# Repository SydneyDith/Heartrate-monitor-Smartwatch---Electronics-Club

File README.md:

# Heart rate Monitor Smartwatch - Electronics Club
Led the development of a heart rate monitor smartwatch based on the ATmega328P microcontroller with a group of 4. Utilized several sensors to send/receive data via I2C communication protocol using C based Arduino IDE. Designed custom PCB while analyzing several datasheets to reduce device size and create a more ergonomic user experience. 

This project was separated into two teams. Team 1 specialized in hardware development and was responsible for component selection, power distribution, datasheet analysis and PCB design. Team 2 interfaced with the microcontroller and sensors in the Arduino IDE by utilizing libraries like PulseSensor Playground, U8g2, and RTClib. While I primarily led Team 1, I also served as the mediator for cross-team communication to ensure hardware and software supported each other.

## Smartwatch Project Objectives

| Feature | Description | Goal |
| :--- | :--- | :--- |
| **Heart Rate Monitor** | Integrate Pulse Sensor | Provides heart rate measurements. |
| **OLED Display** | 1.3" SH1106 OLED Display | Clear visual output for biometric data and time. |
| **Timekeeping** | RTC (Real-Time Clock) | Maintain precise time and date. |
| **Power System** | Rechargeable LiPo | Provides rechargeable power. |

Throughout every iteration of this project we may have moved forward with different components that better fit our needs, however, the 4 underlying features above were included in every version of this project. 

## Proof of Concept: ***May 2025***

The image above shows the first prototype of our Smartwatch. This version was based off of Arduino's smallest dev board the Pro Mini which houses the ATmega328P as its microcontroller (we would later use on the final versions of our project). To provide the functionalities we desired, we ordered several Arduino compatible modules that we could power and hook up to specific digital pins on the Pro Mini. In the table below is the comprehensive parts list we used for our first prototype:

| Feature | Part Name | Image |
| :--- | :--- | :--- |
| **Microcontroller** | Arduino Pro Mini |  |
| **Heart Rate Monitor** | Integrate Pulse Sensor | |
| **OLED Display** | OLED Display |  |
| **Timekeeping** | RTC (Real-Time Clock) | |
| **Power System** | Rechargeable LiPo | |

### Pulse Sensors Issues
The OLED display shows time, date, and current heart rate reading. Team 2 was able to program the Pro Mini to read from the RTC module and pulse sensor then display the results on the OLED. The pulse sensor results fluctuated quite a bit. After some research, we attributed this to the quality of the sensor itself. Many cheap pulse sensors use a method called photoplethysmography (PPG) to measure the change in blood volume in your capillaries as your heart beats. The pulse sensor module uses a green LED to shine light into the capillaries and measures the amount of light reflected back using a photodetector. Ideally, the pulse sensor can translate this information into an accurate heart rate reading. PPG is cheap, however, it's very sensitive to real world motion, ambient light interference and sensor contact. 
[*references*](https://www.sciencedirect.com/topics/engineering/sensor-pulse#:~:text=A%20pulse%20sensor%20is%20defined,Arduino%20for%20health%20monitoring%20applications.)

More accurate pulse sensors (professional grade) cost hundreds or thousands of dollars. Luckily, there is a cheaper PPG option, the MAX30102, that uses multi-wavelength LEDs and has an on-board processing IC. It also includes SpO2 readings as an added feature. We later decided to switch to the MAX30102 pulse oximeter to replace the pulse sensor module.

### First Prototype: ***May 2025***
To turn our breadboard prototype into something that resembled a watch, we soldered the modules together trying to keep wires as short as possible. The following video shows the result:

| Top View | Side View 1 | Side View 2 | Video |
| :---: | :---: | :---: | :---: |
|  |  |  | <video src="https://github.com/user-attachments/assets/febb02ad-0546-478b-9966-6aa6d14cd212" width="120" controls></video> |

During this stage of the design process, my team and I realized that size was going to be our main constraint. The form factor shown above is ridiculously large to be comfortably worn on the wrist. After the 3D printed housing, my team and I estimated our first prototype's dimensions would be around 45mm x 45mm x 50mm, which would better be used as a desk clock. After doing more research and conversing amongst ourselves and with our peers, we decided to create a custom PCB that would eliminate many of the unnecessary functions our sensor modules included. For example, the Pro Mini included headers for every I/O pin, only ~5 of which were essential and the DS3231 RTC module included alarm and 32kHz square wave output functionalities that were out of the scope of this project. By creating a custom PCB, we could limit unnecessary functions of our modules, reducing size and creating a more ergonomic design.

## Schematic Design: ***February 2026***

Although we decided to transition to the MAX30102 pulse oximeter, our proof of concept was still valid as we are only replacing the pulse sensor and there are countless resources online showing the MAX30102's compatibility with the 328P. With this, we decided to move forward into PCB design for our second prototype.

To minimize the size of our PCB, we only wanted to include functionalities that were (for the most part) strictly necessary for our smartwatch. We would essentially be stripping the modules from our prototype and putting everything on one PCB. First, we researched the bare minimum requirements for the ATmega328P microcontroller. Using the microcontroller's datasheet and online resources, we were able to simplify the circuit down to a few capacitors and a pull-up resistor. There was an optional 16MHz external crystal oscillator that was typically used with the 328P, however, these clock speeds wouldn't be necessary for our use case. We could instead use the 8 MHz internal oscillator. We used similar techniques to reduce the size of our RTC and sensor modules.

The final schematic for Prototype 2 is shown below: (*see below the image for in-depth detail about the schematic*)

<p align="center">
  <a href="./images/schem.pdf">📄 View Full Schematic (PDF)</a>
</p>

To use the 328P's 8 MHz internal clock, we were required to run the microcontroller at 3.3V, however, our LiPo was 4.2V-3.7V. To fix this, we simply included a 3.3V Low Dropout regulator (LDO) (U2) after the power switch. This reduced our input voltage to a clean 3.3V. Additionally, the MAX30102 operates at 1.8V, so we included a second LDO (U5) that reduced the 3.3V line to 1.8V which could be used for the pulse oximeter's input voltage. However, every other IC was powered by the 3.3V line. The I2C communication lines from the RTC and pulse oximeter required two 4.7k pull-up resistors to the 3.3V line as per the datasheets. We also included several input capacitors and decoupling capacitors on the RTC and pulse oximeter as the datasheet heavily recommended or required them. 

We also included 4 pin headers: I2C clock, I2C data, +3.3V, and GND for the SH1106 OLED display. We plan to solder the 4 required pins directly to the OLED module used in the previous prototype. 

Since there is no longer a Micro USB port on our microcontroller (like the Pro Mini), we must use a [USB to Serial Converter](https://www.amazon.com/NOYITO-CP2102-Converter-Downloader-Arduino/dp/B07D54K82D) so we can connect and upload code to the 328P using UART communication. 

Upon doing further research on the microcontroller, we encountered a problem. Factory new ATmega328P chips often do not come with a pre-installed bootloader. The bootloader is an essential piece of software that allows the microcontroller to communicate via UART. Without UART communication, we would not be able to upload our code using the USB to serial converter. We researched methods to solve this issue. We found a process called In-System Programming (ISP) that requires an Arduino to flash the bootloader onto a blank ATmega328P. To do this we simply created 4 more pin headers that connected to specific pins on the 328P. These were: MOSI, MISO, SCK, and RESET. Using these four SPI pins alongside +3.3V, and GND, we could successfully bootload the chip using an external Arduino Nano allowing us to program through UART communication.
[Bootloader Procedure (PDF)](images/Smartwatch%20Bootloader%20Procedure.pdf).

## PCB Design: ***April 2026***

Final PCB design: (46mm x 39mm x 5mm)

| Front PCB view (*OLED will be connected to the 4 pinheaders*) | Back PCB view |
| :---: | :---: |
|  |  |

The images and 3D renders above show the final PCB design for Prototype 2. Now I plan to move on to the assembly phase when the PCB and components arrive in the coming weeks.
## TO DO

- [ ] **Bootload the ATmega328P**
    - Follow the [bootloader procedure](images/Smartwatch%20Bootloader%20Procedure.pdf)
    - Ensure the microcontroller communicates via UART
    - Test Blink sketch with on-board LED
- [ ] **Initial Soldering & Assembly**
    - Solder MAX30102 and coin cell battery using a heat gun
    - Assemble the remainder of the PCB
    - Verify MAX30102 has a clear line of sight to the user's skin
- [ ] **Sensor Testing**
    - [ ] Pulse Oximeter: Verify accurate heart rate/SpO2 readings
    - [ ] OLED: Ensure proper display rendering
    - [ ] RTC: Confirm accurate timekeeping
- [ ] **Power System Setup**
    - Integrate LiPo battery and external charging circuit
- [ ] **Performance Testing**
    - [ ] Heart rate accuracy
    - [ ] Battery life duration
    - [ ] Charge time verification
- [ ] **Housing**
    - Design 3D printed enclosure
- [ ] **Interpret Tests**
    - Document changes for Prototype 3

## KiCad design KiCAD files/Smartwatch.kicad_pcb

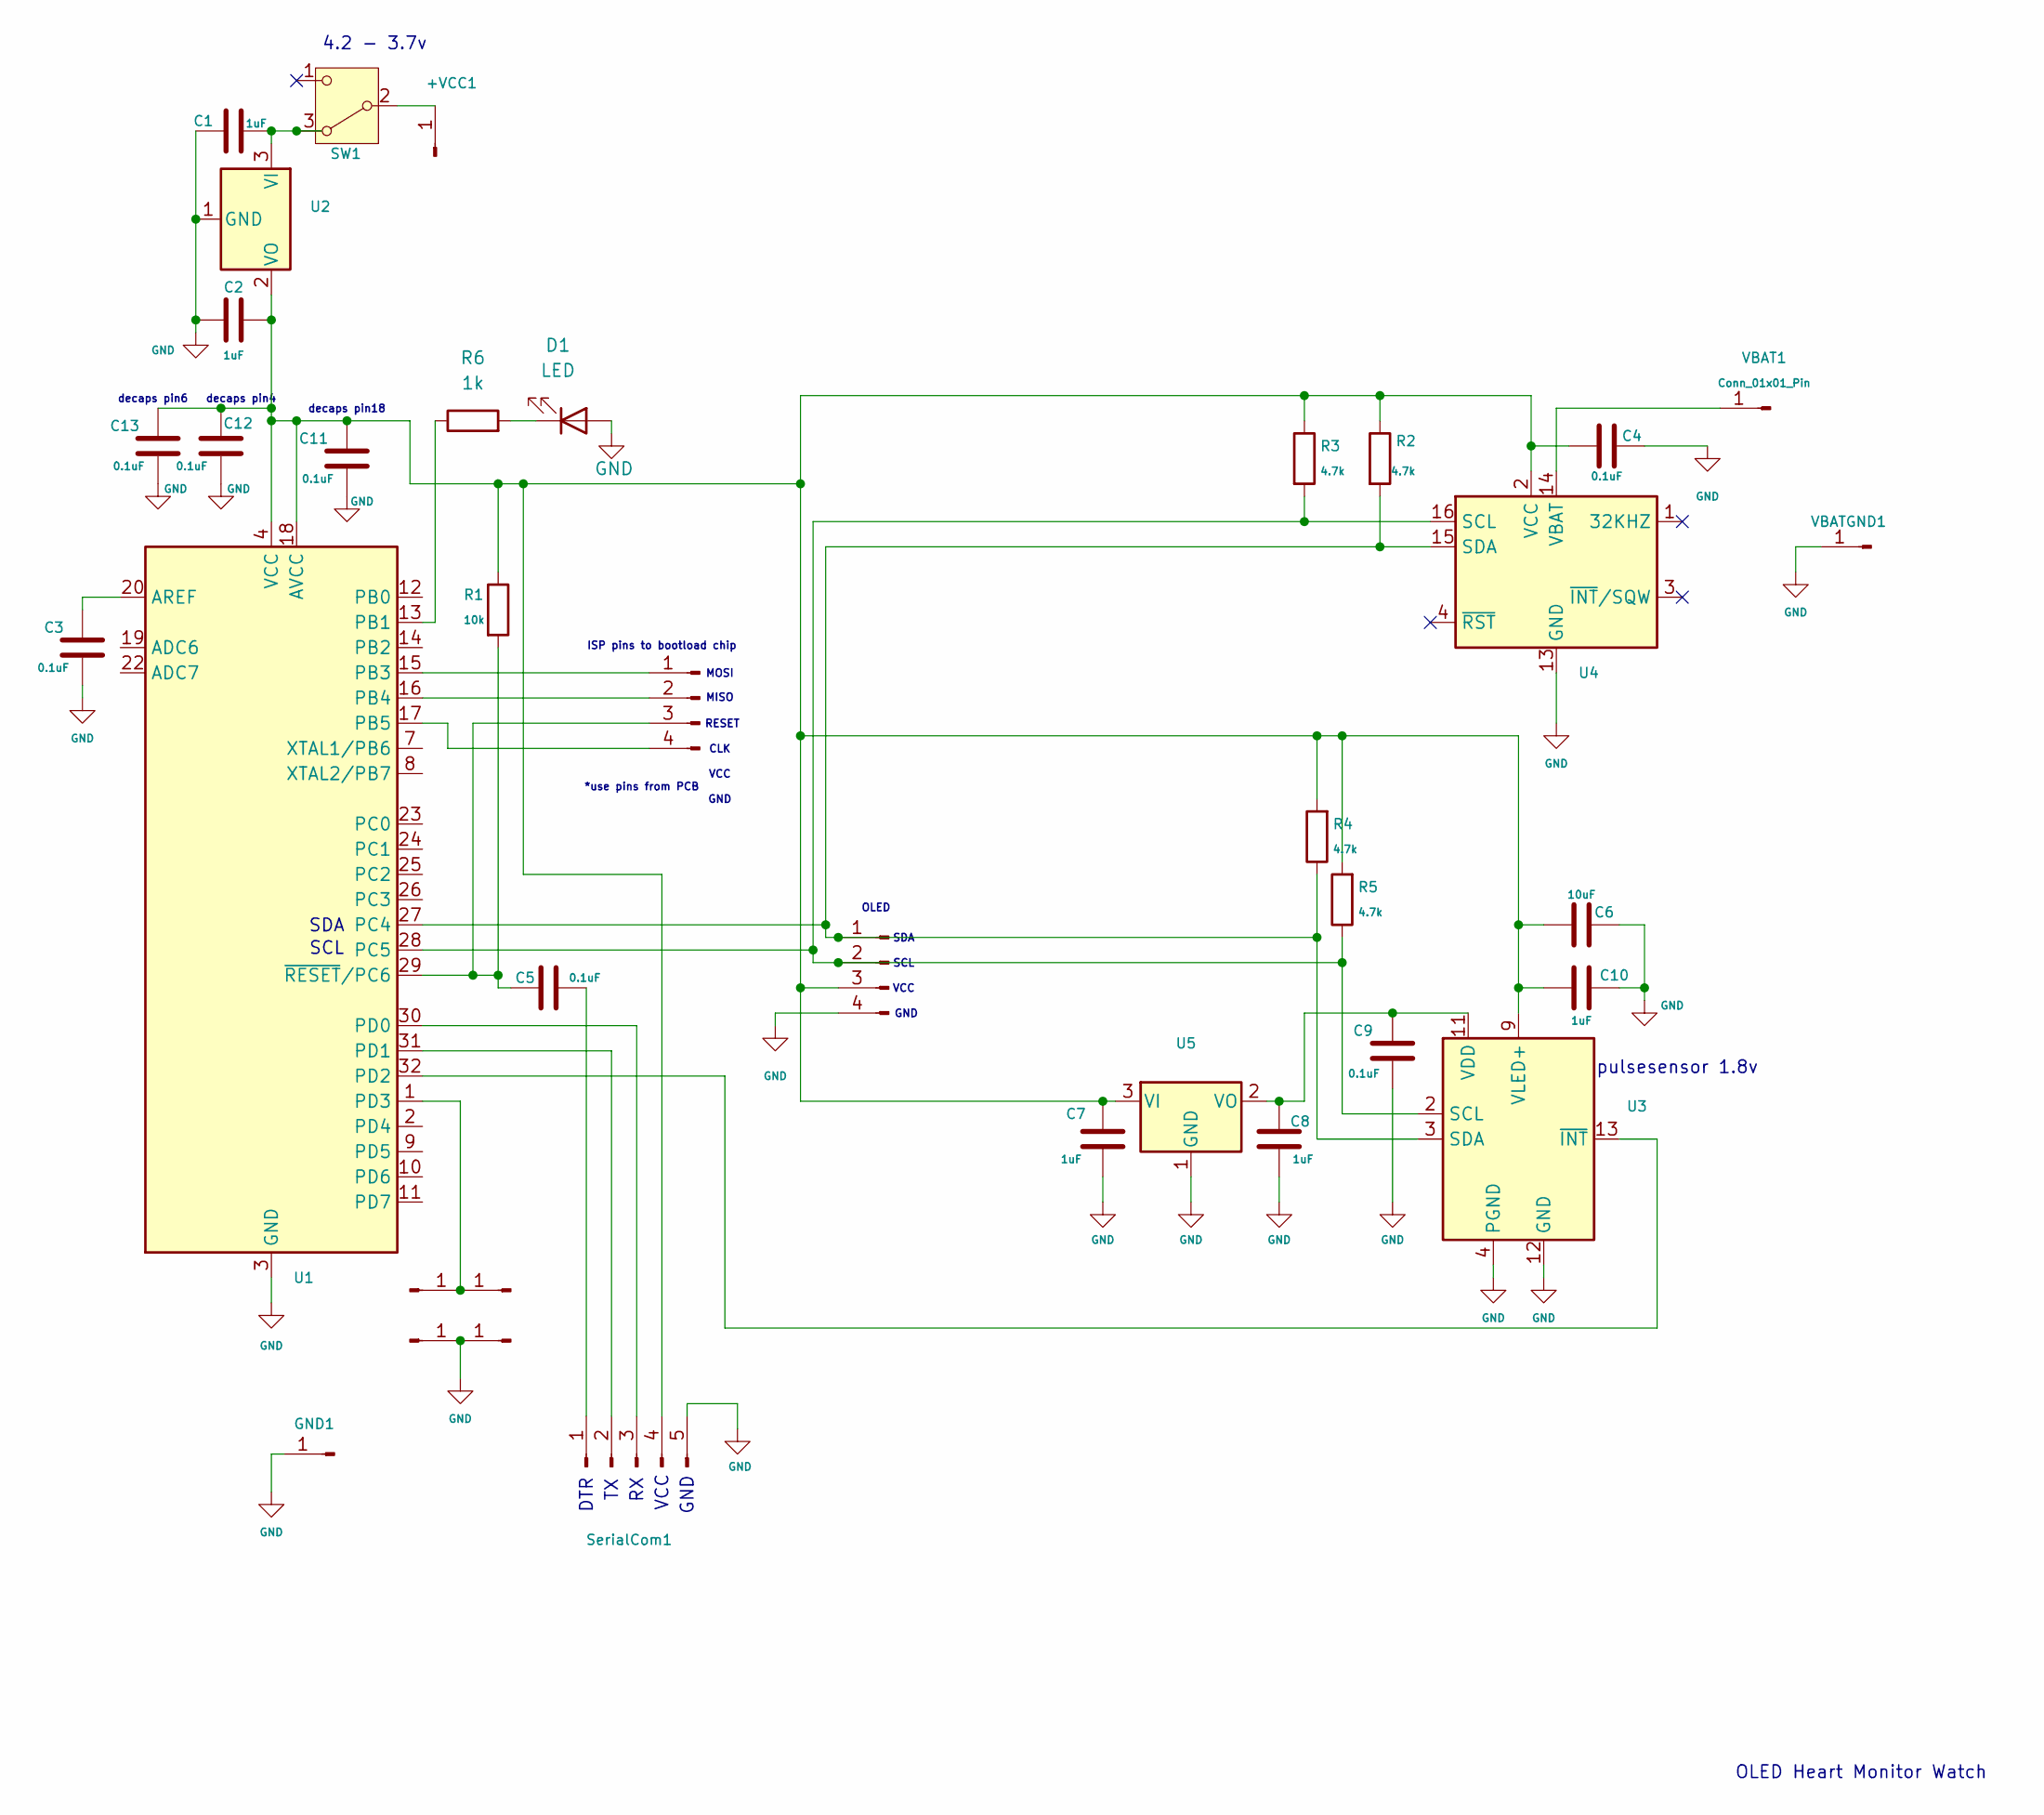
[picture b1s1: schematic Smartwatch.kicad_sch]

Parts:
+VCC1: Conn_01x01_Pin; SolderWire-0.1sqmm_1x01_D0.4mm_OD1mm
Button1, Button2, Button3, Button4: Conn_01x01_Pin; SolderWire-0.1sqmm_1x01_D0.4mm_OD1mm
C1, C2, C7, C8, C10: 1uF; C_0603_1608Metric_Pad1.08x0.95mm_HandSolder
C3, C4, C5, C9, C11, C12, C13: 0.1uF; C_0603_1608Metric_Pad1.08x0.95mm_HandSolder
C6: 10uF; C_0603_1608Metric_Pad1.08x0.95mm_HandSolder
D1: LED; LED_0603_1608Metric_Pad1.05x0.95mm_HandSolder
GND1: Conn_01x01_Pin; SolderWire-0.1sqmm_1x01_D0.4mm_OD1mm
OLED1, OLED2: Conn_01x04_Pin; SolderWire-0.1sqmm_1x04_P3.6mm_D0.4mm_OD1mm
R1: 10k; R_0603_1608Metric_Pad0.98x0.95mm_HandSolder
R2, R3, R4, R5: 4.7k; R_0603_1608Metric_Pad0.98x0.95mm_HandSolder
R6: 1k; R_0603_1608Metric_Pad0.98x0.95mm_HandSolder
SW1: SW_Nidec_CAS-120A1; SW_Slide_SPDT_Angled_CK_OS102011MA1Q
SerialCom1: Conn_01x05_Pin; SolderWire-0.1sqmm_1x05_P3.6mm_D0.4mm_OD1mm
U1: ATmega328P-A; TQFP-32_7x7mm_P0.8mm
U2: MCP1700x-330xxTT; SOT-23
U3: MAX30102; Maxim_OLGA-14_3.3x5.6mm_P0.8mm
U4: DS3231M; SOIC-16W_7.5x10.3mm_P1.27mm
U5: MCP1700x-180xxTT; SOT-23
VBAT1: Conn_01x01_Pin; SolderWire-0.1sqmm_1x01_D0.4mm_OD1mm
VBATGND1: Conn_01x01_Pin; SolderWire-0.1sqmm_1x01_D0.4mm_OD1mm

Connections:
GND: Button3.1, Button4.1, C1.1, C2.2, C3.2, C4.2, C6.2, C7.1, C8.1, C9.1, C10.2, C11.2, C12.2, C13.2, D1.2 (A), GND1.1, OLED1.4, SerialCom1.5, U1.3 (GND), U1.5 (GND), U1.21 (GND), U2.1 (GND), U3.4 (PGND), U3.12 (GND), U4.5 (GND), U4.6 (GND), U4.7 (GND), U4.8 (GND), U4.9 (GND), U4.10 (GND), U4.11 (GND), U4.12 (GND), U4.13 (GND), U5.1 (GND), VBATGND1.1
unnamed: +VCC1.1, SW1.2 (B)
unnamed: Button1.1, Button2.1, U1.1 (PD3)
unnamed: D1.1 (K), R6.2
unnamed: OLED1.1, R2.2, R4.1, U1.27 (PC4), U3.3 (SDA), U4.15 (SDA)
unnamed: OLED1.2, R3.2, R5.1, U1.28 (PC5), U3.2 (SCL), U4.16 (SCL)
unnamed: C2.1, C4.1, C6.1, C7.2, C10.1, C11.1, C12.1, C13.1, OLED1.3, R1.1, R2.1, R3.1, R4.2, R5.2, SerialCom1.4, U1.4 (VCC), U1.6 (VCC), U1.18 (AVCC), U2.2 (VO), U3.9 (VLED+), U3.10 (VLED+), U4.2 (VCC), U5.3 (VI)
unnamed: OLED2.1, U1.15 (PB3)
unnamed: OLED2.2, U1.16 (PB4)
unnamed: C5.2, OLED2.3, R1.2, U1.29 (~RESET/PC6)
unnamed: OLED2.4, U1.17 (PB5)
unnamed: C1.2, SW1.3 (A), U2.3 (VI)
unnamed: C5.1, SerialCom1.1
unnamed: SerialCom1.2, U1.31 (PD1)
unnamed: SerialCom1.3, U1.30 (PD0)
unnamed: C3.1, U1.20 (AREF)
unnamed: R6.1, U1.13 (PB1)
unnamed: U1.32 (PD2), U3.13 (~INT)
unnamed: C8.2, C9.2, U3.11 (VDD), U5.2 (VO)
unnamed: U4.14 (VBAT), VBAT1.1

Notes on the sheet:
4.2 - 3.7v
MOSI
CLK
MISO
VCC
VCC
SCL
SDA
GND
*use pins from PCB
OLED Heart Monitor Watch
pulsesensor 1.8v
decaps pin4
decaps pin18
decaps pin6
ISP pins to bootload chip
DTR
OLED
RESET

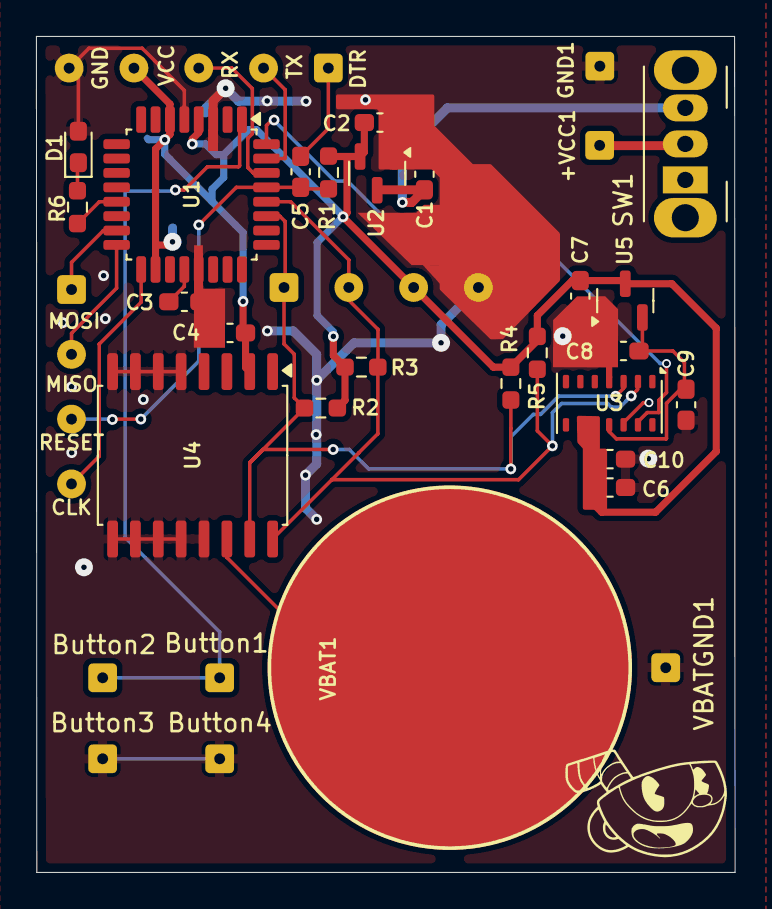
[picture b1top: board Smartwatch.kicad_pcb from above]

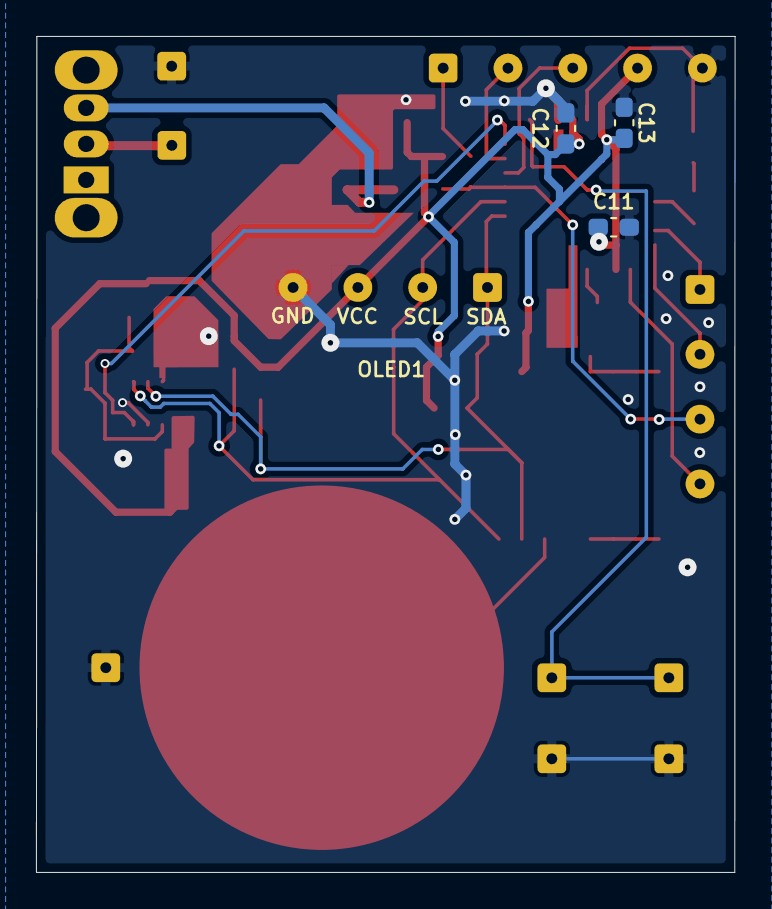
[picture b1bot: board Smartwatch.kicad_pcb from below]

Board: 2 copper layers, 38.8 x 46.4 mm, 37 parts (4 on the bottom side), 20 nets.

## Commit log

2026-04-07 Rename Smartwatch.pdf to schem.pdf
2026-04-07 Rename schem.pdf to images/schem.pdf
2026-04-08 Rename arduinopromicro.jpg to arduinopromini.jpg
